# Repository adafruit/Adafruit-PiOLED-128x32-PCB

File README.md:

## Adafruit PiOLED 128x32 PCB

<a href="http://www.adafruit.com/products/3527"><br/>
Click here to purchase one from the Adafruit shop</a>

PCB files for the Adafruit PiOLED 128x32. Format is EagleCAD schematic and board layout
* http://www.adafruit.com/product/3527

### Description

If you're looking for the most compact li'l display for a Raspberry Pi (most likely a Pi Zero) project, this might be just the thing you need!

The Adafruit 128x32 PiOLED is your little OLED pal, ready to snap onto any and all Raspberry Pi computers, to give you a little display. The PiOLED comes with a monochrome 128x32 OLED, with sharp white pixels. The OLED uses only the I2C pins so you have plenty of GPIO connections available for buttons, LEDs, sensors, etc. It's also nice and compact so it will fit into any case.

These displays are small, only about 1" diagonal, but very readable due to the high contrast of an OLED display. This screen is made of 128x32 individual white OLED pixels and because the display makes its own light, no backlight is required. This reduces the power required to run the OLED and is why the display has such high contrast; we really like this miniature display for its crispness!

Using the display is very easy, we have a Python library for the SSD1306 chipset. Our example code allows you to draw images, text, whatever you like, using the Python imaging library. Our tests showed 30 FPS update rates so you can do animations or simple video.

Comes completely pre-assembled and tested so you don't need to do anything but plug it in and install our Python code! Works with any Raspberry Pi computer, including the original Pi 1, B+, Pi 2, Pi 3 and Pi Zero.

### License

Adafruit invests time and resources providing this open source design, please support Adafruit and open-source hardware by purchasing products from [Adafruit](https://www.adafruit.com)!

Designed by Limor Fried/Ladyada for Adafruit Industries.

Creative Commons Attribution/Share-Alike, all text above must be included in any redistribution. See license.txt for additional details.

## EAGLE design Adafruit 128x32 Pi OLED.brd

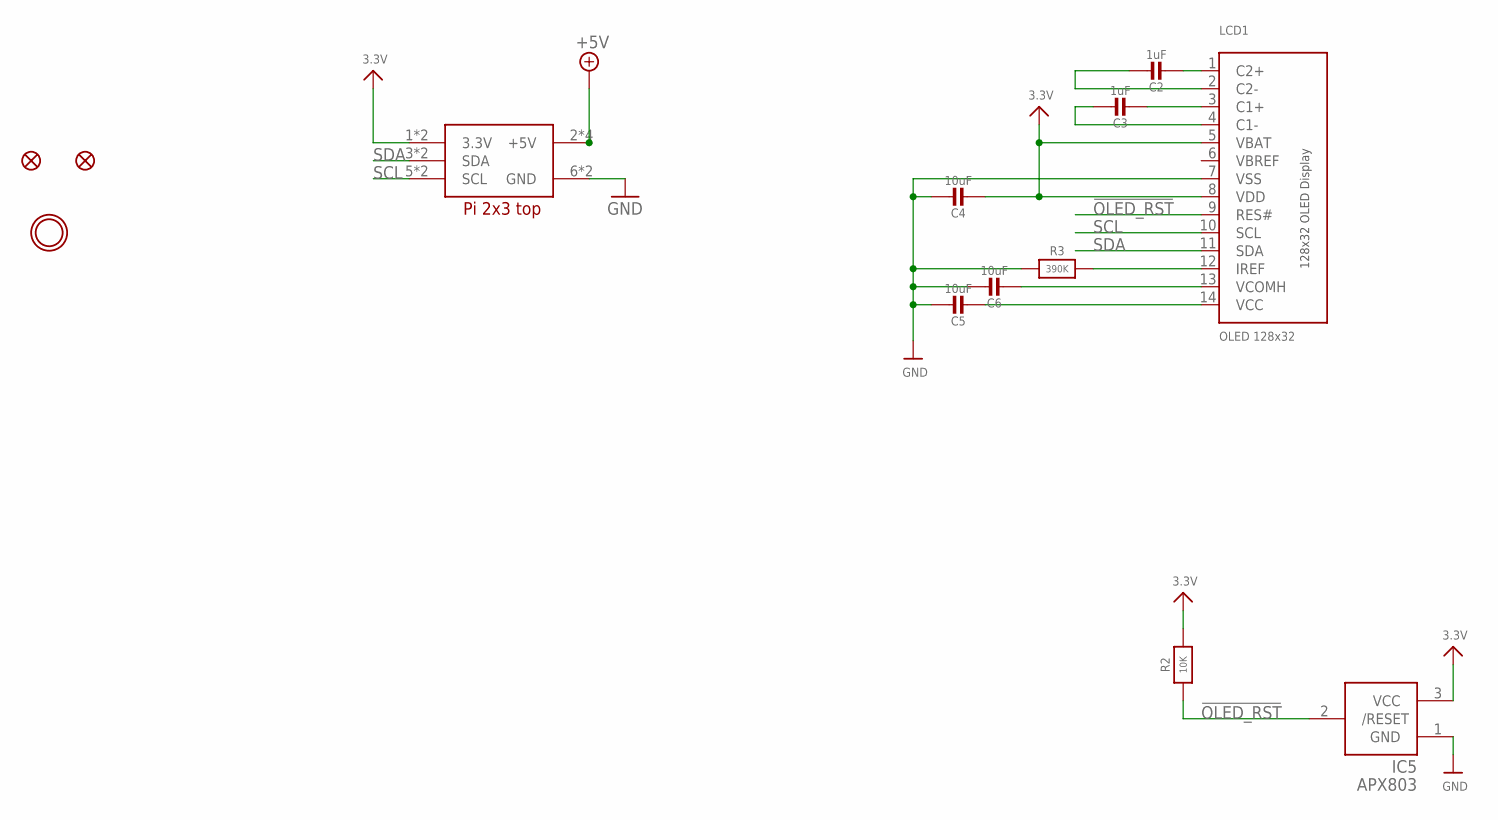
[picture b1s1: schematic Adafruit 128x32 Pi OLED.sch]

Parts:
C2, C3: 1uF; 0805-NO
C4, C5, C6: 10uF; 0805-NO
FID3, FID4: FIDUCIAL_1MM
IC5: APX803; SOT23
LCD1: OLED 128x32; UG-2832HSWEG02_WRAPUNDER
R2: 10K; 0805-NO
R3: 390K; 0805-NO
RPI1: RASPBERRYPI_2X3; RASPBERRYPI_2X3_THMSMT
U$4: MOUNTINGHOLE3.0THIN; MOUNTINGHOLE_3.0_PLATEDTHIN

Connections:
3.3V: C4.2, IC5.3 (VCC), LCD1.5 (VBAT), LCD1.8 (VDD), R2.2, RPI1.1 (3.3V), RPI1.1' (3.3V)
!OLED_RST: IC5.2 (/RESET), LCD1.9 (RES#), R2.1
+5V: RPI1.2 (+5V), RPI1.2' (+5V), RPI1.4 (+5V), RPI1.4' (+5V)
GND: C4.1, C5.1, C6.1, IC5.1 (GND), LCD1.7 (VSS), R3.1, RPI1.6 (GND), RPI1.6' (GND)
unnamed: C2.2, LCD1.1 (C2+)
unnamed: C2.1, LCD1.2 (C2-)
unnamed: C3.2, LCD1.3 (C1+)
unnamed: C3.1, LCD1.4 (C1-)
unnamed: C6.2, LCD1.13 (VCOMH)
unnamed: C5.2, LCD1.14 (VCC)
unnamed: LCD1.12 (IREF), R3.2
SCL: LCD1.10 (SCL), RPI1.5 (SCL), RPI1.5' (SCL)
SDA: LCD1.11 (SDA), RPI1.3 (SDA), RPI1.3' (SDA)
VBREF: LCD1.6 (VBREF)

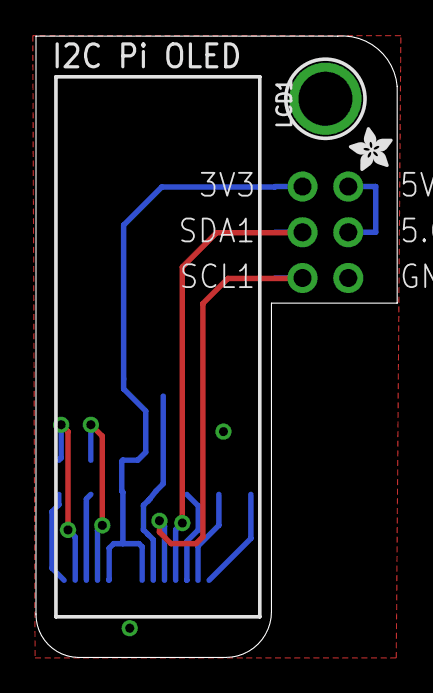
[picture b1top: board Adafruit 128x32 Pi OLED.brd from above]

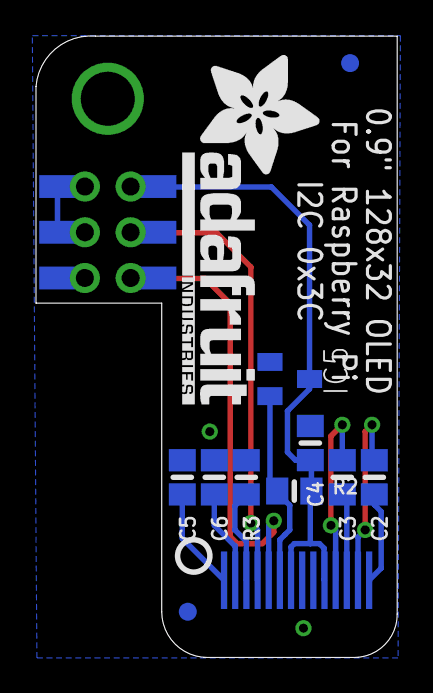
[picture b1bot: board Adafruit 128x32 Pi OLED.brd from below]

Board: 2 copper layers, 20.1 x 34.5 mm, 16 parts (12 on the bottom side), 13 nets.

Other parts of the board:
U$1: ADAFRUIT_2.5MM
U$3: PCBFEAT-REV-040
U$8: ADAFRUIT_TEXT_20MM

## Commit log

2017-05-31 init!
2017-05-31 read me!

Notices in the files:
parts and their libraries:
microbuilder: This work is placed in the public domain, and may be freely used for commercial and non-commercial work with the following conditions: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
